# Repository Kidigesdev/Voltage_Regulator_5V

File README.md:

# Voltage_Regulator_5V

A small and simple voltage regulator on its own PCB.

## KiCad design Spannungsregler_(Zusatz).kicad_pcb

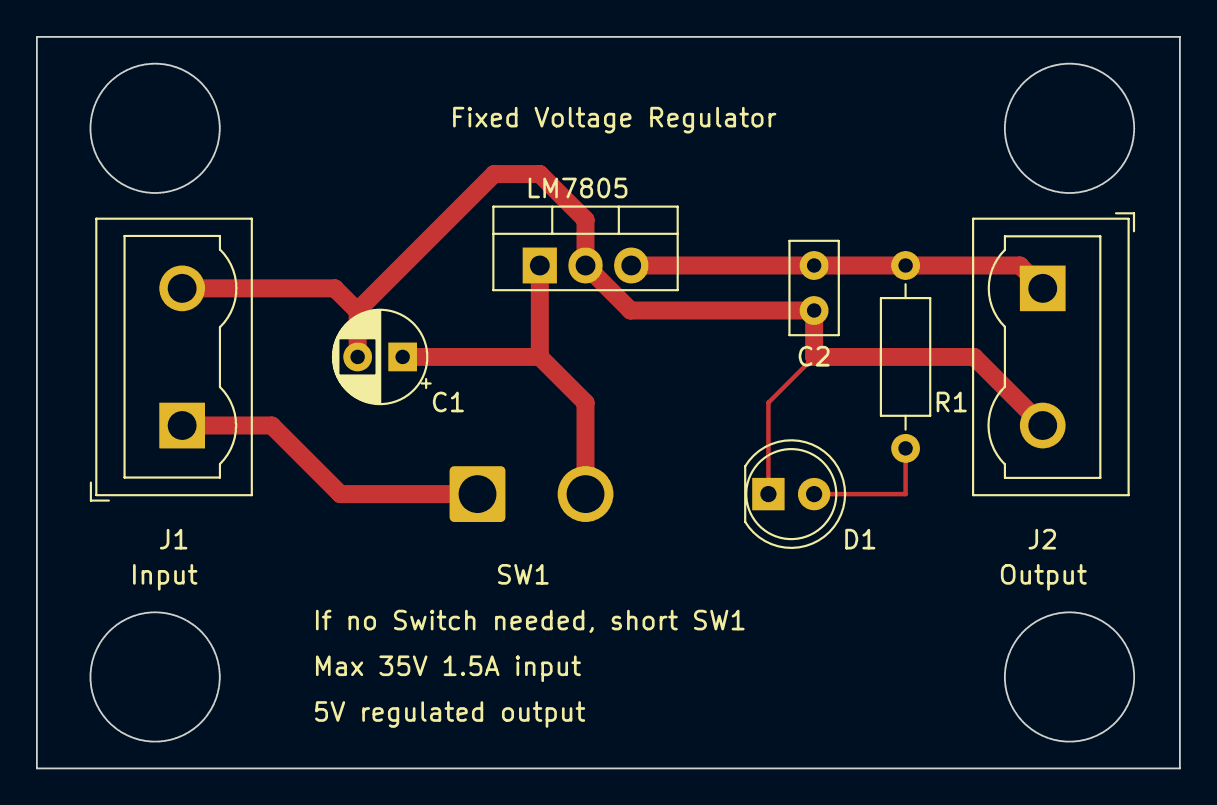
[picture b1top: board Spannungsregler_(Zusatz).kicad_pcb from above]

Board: 2 copper layers, 63.5 x 40.6 mm, 8 parts (0 on the bottom side), 5 nets.

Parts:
C1: C_Polarized; CP_Radial_D5.0mm_P2.50mm
C2: C2; C_Disc_D5.0mm_W2.5mm_P2.50mm
D1: LED; LED_D5.0mm
J1, J2: Screw_Terminal_01x02; TerminalBlock_Wuerth_691311400102_P7.62mm
LM7805: LM7805_TO220; TO-220-3_Vertical
R1: R; R_Axial_DIN0207_L6.3mm_D2.5mm_P10.16mm_Horizontal
SW1: SW_DIP_x01; SolderWire-1.5sqmm_1x02_P6mm_D1.7mm_OD3mm

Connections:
unnamed: D1.2 (A), R1.1
unnamed: C1.2, C2.2, D1.1 (K), J1.2, J2.2, LM7805.2 (GND)
unnamed: J1.1, SW1.1
unnamed: C2.1, J2.1, LM7805.3 (VO), R1.2
unnamed: C1.1, LM7805.1 (VI), SW1.2

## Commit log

2023-10-07 Add files via upload
    First Upload of all the data
